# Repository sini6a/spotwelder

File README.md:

# Open Source Spot Welder

An easy-to-assemble, through-hole spot welder capable of switching high currents for welding nickel strip to lithium-ion cells. Controlled by an ATtiny13 microcontroller.

The welder is powered by a 12 V car battery or another suitable high-current battery source. The PCB, schematic, firmware, enclosure, and fabrication files are included in this repository.

> [!WARNING]
> This project switches extremely high current from a battery. Incorrect wiring, insufficient conductors, short circuits, or excessive pulse duration can cause fire, burns, damaged cells, destroyed MOSFETs, or battery failure.

## Sponsor

PCB fabrication for this project was sponsored by [PCBWay](https://www.pcbway.com/).

## Features

* **Eight-MOSFET switching bank**
  Eight IRF1404 N-channel MOSFETs are connected in parallel to switch the welding current. Each MOSFET has an individual 10 Ω gate resistor to help control switching and reduce gate ringing.

* **Dedicated MOSFET gate driver**
  An MCP1407 drives all eight MOSFET gates simultaneously. A hardware pull-down resistor on the driver input keeps the MOSFET bank off while the microcontroller is starting, resetting, or unpowered.

* **Automatic touch-to-weld triggering**
  A PC817 optocoupler-based sensing circuit detects when both welding probes are in contact with a conductive workpiece. The isolated output signals the ATtiny13 to begin the welding sequence.

* **Adjustable 1–10 ms main pulse**
  A pushbutton connected to TP4 cycles the main weld-pulse duration from 1 to 10 ms.

* **EEPROM setting storage**
  The selected weld duration is saved in the ATtiny13 EEPROM and restored after the welder is disconnected from power.

* **LED and buzzer feedback**
  The onboard LED and passive piezo buzzer provide startup, welding, and setting-change feedback. When the duration is changed, the LED flashes and the buzzer beeps once for each selected millisecond.

* **Optional double-pulse welding**
  The firmware can produce a short pre-pulse followed by the adjustable main pulse. The pre-pulse can help settle the probe contact before the main weld.

* **Separated control and power grounds**
  The high-current welding ground (`GND`) and logic ground (`CTRL_GND`) are routed separately and joined at a single net-tie point to reduce switching noise at the microcontroller.

* **Reverse-polarity protection**
  A 1N5819 Schottky diode protects the 5 V control supply if the battery input is accidentally connected with reversed polarity.

* **Transient suppression**
  Four 5.0SMDJ14A TVS diodes help clamp voltage transients generated by the welding cables and other parasitic inductance when the MOSFET bank switches off.

* **Large high-current connection pads**
  The battery and welding connections use large exposed copper pads intended for soldered or mechanically secured high-current conductors.

* **Four-layer PCB**
  Copper zones on F.Cu, In1.Cu, In2.Cu, and B.Cu help distribute the short welding-current pulses through the MOSFET bank.

> [!IMPORTANT]
> PCB copper alone should not be treated as a complete high-current busbar. Thick copper cable, copper braid, copper strip, or another suitable reinforcement is recommended for the main battery and electrode current paths.

## How it works

1. **Power input**
   A 12 V car battery or another suitable high-current battery source is connected to the `IN/OUT+` and `IN-` pads.

2. **Probe contact detection**
   When both welding probes contact the conductive workpiece, the PC817 sensing circuit produces an isolated trigger signal for the ATtiny13.

3. **Trigger validation**
   The firmware verifies that the contact signal remains active for the configured debounce period.

4. **Pre-pulse**
   When double-pulse mode is enabled, the ATtiny13 briefly activates the MCP1407 and MOSFET bank for the configured pre-pulse duration.

5. **Pulse gap**
   The MOSFETs switch off for a short interval before the main pulse.

6. **Main weld pulse**
   The MOSFET bank switches on for the selected duration between 1 and 10 ms, passing a short burst of high current through the nickel strip and cell connection.

7. **Feedback and cooldown**
   The buzzer and LED confirm that the weld sequence completed. The firmware then enforces a cooldown period and waits for the probes to be lifted before another weld can begin.

## Weld-time adjustment

TP4 is used to change the main weld-pulse duration.

Each complete button press advances the setting by 1 ms:

```text
1 → 2 → 3 → 4 → 5 → 6 → 7 → 8 → 9 → 10 → 1 ms
```

After the value changes:

* The setting is saved to EEPROM.
* The LED flashes once per selected millisecond.
* The buzzer beeps at the same time as each flash.

For example, a 6 ms setting produces six LED flashes and six beeps.

The displayed value represents the **main pulse only**. When double-pulse mode is enabled, the fixed pre-pulse is added separately.

## Firmware

The firmware is located at:

```text
Firmware/main.c
```

It directly controls:

* The MCP1407 gate-driver input
* The PC817 automatic weld trigger
* The TP4 settings button
* The status LED
* The passive piezo buzzer
* EEPROM storage for the selected duration

The firmware forces the MOSFET-driver control pin low during startup. This works together with the hardware pull-down resistor on the MCP1407 input to reduce the risk of an unintended weld pulse during reset or power-up.

### Default configuration

| Definition                | Default | Description                                          |
| ------------------------- | ------: | ---------------------------------------------------- |
| `WELD_PULSE_MIN_MS`       |    1 ms | Lowest selectable main-pulse duration                |
| `WELD_PULSE_MAX_MS`       |   10 ms | Highest selectable main-pulse duration               |
| `WELD_PULSE_DEFAULT_MS`   |    6 ms | Used when EEPROM does not contain a valid setting    |
| `USE_DOUBLE_PULSE`        |       1 | Enables the pre-pulse and main-pulse sequence        |
| `PRE_PULSE_MS`            |    3 ms | Fixed pre-pulse duration                             |
| `PULSE_GAP_MS`            |   80 ms | Delay between the pre-pulse and main pulse           |
| `WELD_COOLDOWN_MS`        |  800 ms | Minimum delay after a weld before re-arming          |
| `TRIGGER_DEBOUNCE_MS`     |   15 ms | Probe-contact validation time                        |
| `REQUIRE_TRIGGER_RELEASE` |       1 | Requires the probes to be lifted before another weld |
| `BEEP_ON_WELD_MS`         |   60 ms | Weld-confirmation tone duration                      |
| `BUZZER_ACTIVE_TYPE`      |       0 | Configures BZ1 as an externally driven passive piezo |
| `BUZZER_TONE_HZ`          | 4000 Hz | Normal feedback-tone frequency                       |

Review the values in `Firmware/main.c` before flashing, as development versions may use different pre-pulse and timing defaults.

### Building and flashing

The firmware is built with AVR-GCC and optimized for the ATtiny13's limited 1 KB program memory.

```bash
cd Firmware

make
make flash
make fuses
```

The default Makefile targets are:

| Command      | Action                                                                                                |
| ------------ | ----------------------------------------------------------------------------------------------------- |
| `make`       | Build the firmware and generate the HEX file                                                          |
| `make flash` | Flash the firmware over ISP                                                                           |
| `make fuses` | Configure the 9.6 MHz internal oscillator with the divide-by-8 fuse, resulting in a 1.2 MHz CPU clock |

The default programmer configuration may need to be changed in the Makefile when using an Arduino as ISP instead of a USBasp.

## Enclosure

A two-piece enclosure is included and was designed in FreeCAD. 3xM4 Nuts should be installed while printing the enclosure.

| Assembled                                           | Top and bottom                                                        |
| --------------------------------------------------- | --------------------------------------------------------------------- |
|  |  |

The enclosure includes:

* Four mounting bosses
* Screw-together top and bottom sections
* Side openings for the battery and electrode cables
* Source files for modification and 3D printing

Included files:

```text
Enclosure/SpotWelder.FCStd
Enclosure/Top Body.step
Enclosure/Bottom Body.step
```

## Project status

The Rev A hardware has been assembled, powered, and successfully used for spot welding.

The following core functions have been tested:

* ATtiny13 startup
* MOSFET gate-driver control
* Automatic probe-contact triggering
* Timed welding pulses
* LED feedback
* Passive buzzer feedback
* Welding from a 12 V car battery

## License

This project is licensed under the **Creative Commons Attribution-NonCommercial-ShareAlike 4.0 International license**.

See [LICENCE.md](LICENCE.md) for the complete terms.

You may build, modify, and share the design for personal and non-commercial use, provided that attribution is retained and derivative works use the same license.

Commercial production or resale of boards based on this design requires permission from Datakonsulten Sverige AB.

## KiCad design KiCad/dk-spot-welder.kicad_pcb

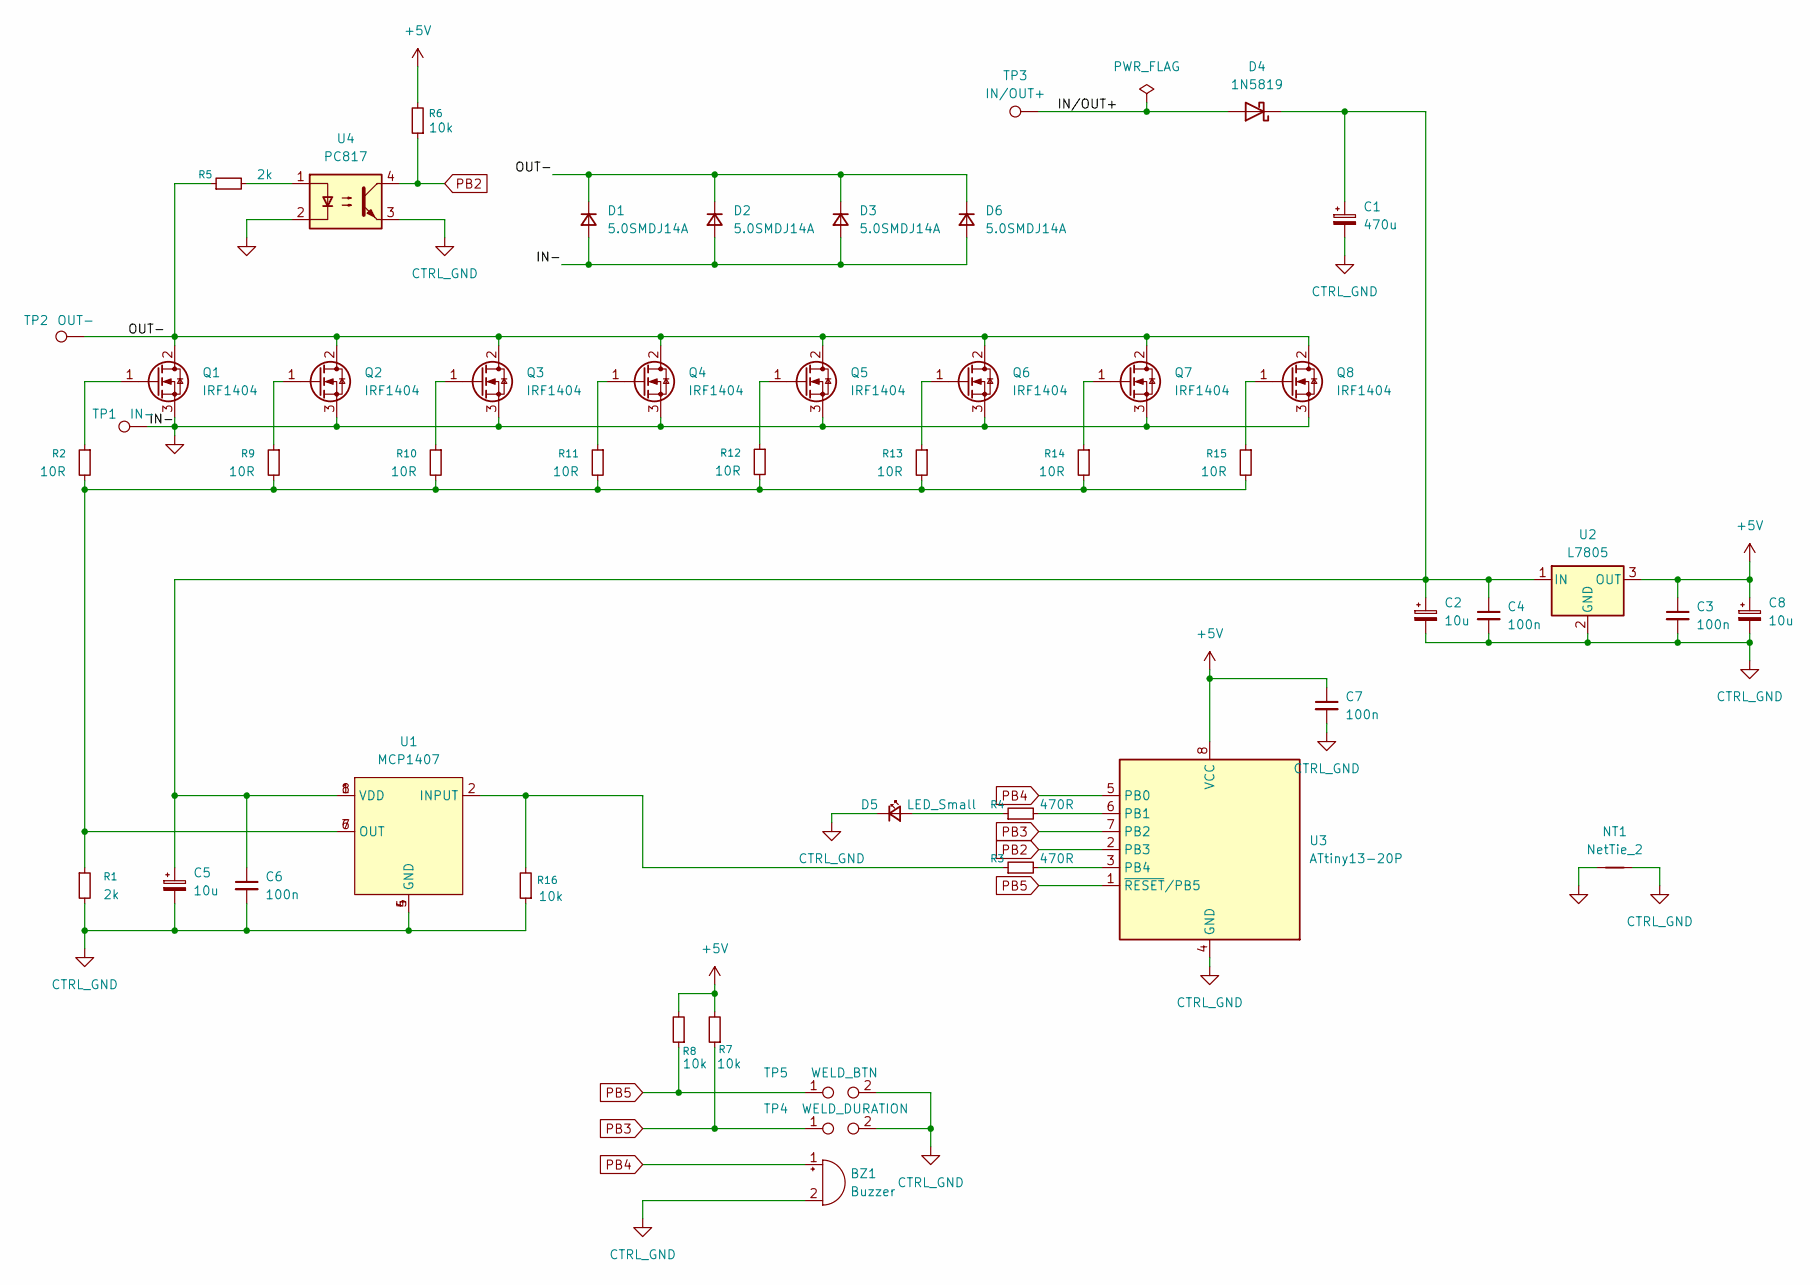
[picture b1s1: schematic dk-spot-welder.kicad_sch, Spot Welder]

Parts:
BZ1: Buzzer; Buzzer_12x9.5RM7.6
C1: 470u; CP_Radial_D10.0mm_P5.00mm
C2, C5, C8: 10u; CP_Radial_D6.3mm_P2.50mm
C3, C4, C6, C7: 100n; C_Disc_D5.0mm_W2.5mm_P5.00mm
D1, D2, D3, D6: 5.0SMDJ14A; D_SMC_Handsoldering
D4: 1N5819; D_DO-41_SOD81_P10.16mm_Horizontal
D5: LED_Small; LED_D3.0mm
NT1: NetTie_2; NetTie-2_THT_Pad1.0mm
Q1, Q2, Q3, Q4, Q5, Q6, Q7, Q8: IRF1404; TO-220-2_Horizontal_TabDown
R1, R5: 2k; R_Axial_DIN0309_L9.0mm_D3.2mm_P12.70mm_Horizontal
R2, R9, R10, R11, R12, R13, R14, R15: 10R; R_Axial_DIN0309_L9.0mm_D3.2mm_P12.70mm_Horizontal
R3, R4: 470R; R_Axial_DIN0309_L9.0mm_D3.2mm_P12.70mm_Horizontal
R6, R7, R8, R16: 10k; R_Axial_DIN0309_L9.0mm_D3.2mm_P12.70mm_Horizontal
TP1: IN-; MountingHole_4mm_Pad_Via
TP2: OUT-; MountingHole_4mm_Pad_Via
TP3: IN/OUT+; MountingHole_4mm_Pad_Via
TP4: WELD_DURATION; TestPoint_2Pads_Pitch5.08mm_Drill1.3mm
TP5: WELD_BTN; TestPoint_2Pads_Pitch5.08mm_Drill1.3mm
U1: MCP1407; DIP-8_W7.62mm
U2: L7805; TO-220-3_Horizontal_TabDown
U3: ATtiny13-20P; DIP-8_W7.62mm
U4: PC817; DIP-4_W7.62mm

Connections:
+5V: C3.1, C7.1, C8.1, R6.2, R7.2, R8.2, U2.3 (OUT), U3.8 (VCC)
/IN/OUT+: D4.2 (A), TP3.1 (1_1)
/OUT-: D1.1 (K), D2.1 (K), D3.1 (K), D6.1 (K), Q1.2 (D), Q2.2 (D), Q3.2 (D), Q4.2 (D), Q5.2 (D), Q6.2 (D), Q7.2 (D), Q8.2 (D), R5.1, TP2.1 (1_1)
CTRL_GND: BZ1.2 (-), C1.2, C2.2, C3.2, C4.2, C5.2, C6.2, C7.2, C8.2, D5.1 (K), NT1.2, R1.2, R16.1, TP4.2, TP5.2, U1.4 (GND), U1.5 (GND), U2.2 (GND), U3.4 (GND), U4.3
GND: D1.2 (A), D2.2 (A), D3.2 (A), D6.2 (A), NT1.1, Q1.3 (S), Q2.3 (S), Q3.3 (S), Q4.3 (S), Q5.3 (S), Q6.3 (S), Q7.3 (S), Q8.3 (S), TP1.1 (1_1), U4.2
unnamed: C1.1, C2.1, C4.1, C5.1, C6.1, D4.1 (K), U1.1 (VDD), U1.8 (VDD), U2.1 (IN)
unnamed: D5.2 (A), R4.1
unnamed: Q1.1 (G), R2.1
unnamed: Q2.1 (G), R9.1
unnamed: Q3.1 (G), R10.1
unnamed: Q4.1 (G), R11.1
unnamed: Q5.1 (G), R12.1
unnamed: Q6.1 (G), R13.1
unnamed: Q7.1 (G), R14.1
unnamed: Q8.1 (G), R15.1
unnamed: R1.1, R2.2, R9.2, R10.2, R11.2, R12.2, R13.2, R14.2, R15.2, U1.6 (OUT), U1.7 (OUT)
unnamed: R5.2, U4.1
unnamed: R3.1, R16.2, U1.2 (INPUT)
unnamed: R4.2, U3.6 (PB1)
unnamed: R3.2, U3.3 (PB4)
PB2: R6.1, U3.2 (PB3), U4.4
PB3: R7.1, TP4.1, U3.7 (PB2)
PB4: BZ1.1 (+), U3.5 (PB0)
PB5: R8.1, TP5.1, U3.1 (~RESET/PB5)

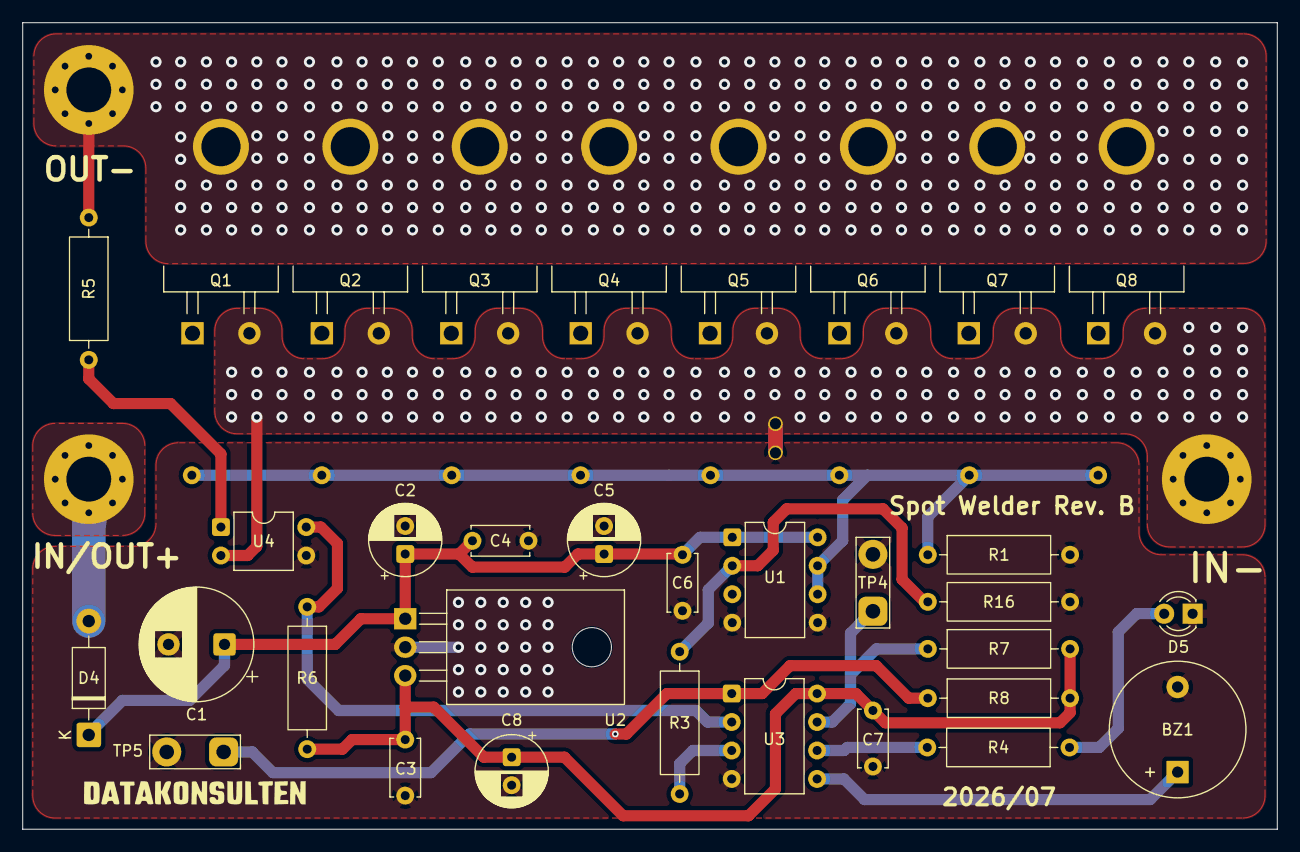
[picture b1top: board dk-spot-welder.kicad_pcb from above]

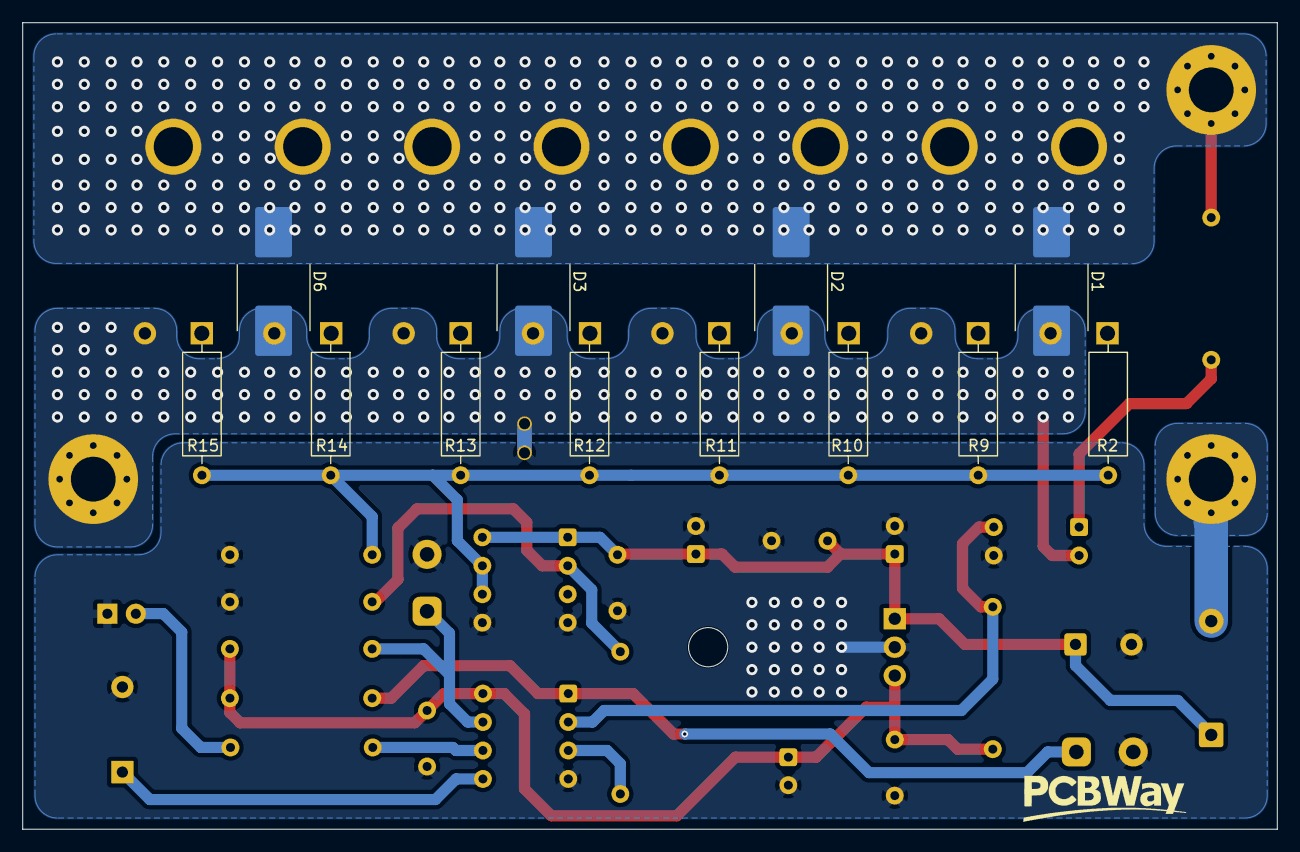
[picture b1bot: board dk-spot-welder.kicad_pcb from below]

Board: 4 copper layers, 112.0 x 72.0 mm, 49 parts (12 on the bottom side), 24 nets.

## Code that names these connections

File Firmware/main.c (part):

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 * Datakonsulten Spot Welder - ATtiny13-20P firmware
 *
 * Pin mapping (derived from KiCad/dk-spot-welder.kicad_sch, U3):
 *   PB0 (pin 5) -> BZ1   buzzer, active HIGH, no series resistor (active/self-oscillating
 *                  piezo buzzer assumed - see BUZZER_ACTIVE_TYPE below)
 *   PB1 (pin 6) -> D5    status LED via R4, active HIGH
 *   PB2 (pin 7) -> TP4   manual trigger button header, external pull-up R7 to +5V,
 *                  active LOW (button pulls to CTRL_GND when pressed)
 *   PB3 (pin 2) -> U4    PC817 phototransistor output, external pull-up R6 to +5V,
 *                  active LOW (opto conducts when welding tips touch the workpiece)
 *   PB4 (pin 3) -> R3 -> U1 MCP1407 INPUT, active HIGH = MOSFET bank ON (welding current
 *                  flowing). R16 hardware-pulls this net low at the driver input as a
 *                  fail-safe, but firmware also forces PB4 low before anything else runs.
 *   PB5 (pin 1) -> RESET, pulled up by R8. Not used as GPIO.
 *
 * All user-tunable parameters are grouped at the top of this file.
 */
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/* ================================================================= */

/* --- Pin assignments (see header comment for derivation) --- */
#define PIN_BUZZER  PB0
#define PIN_LED     PB1
#define PIN_BTN     PB2   /* TP4 weld-duration settings button, active LOW */
#define PIN_OPTO    PB3   /* automatic tip-touch trigger, via U4/PC817 */
#define PIN_WELD    PB4   /* MOSFET bank enable, via U1/MCP1407 */

/* Millisecond delay built from a compile-time-constant _delay_us() call per iteration,
   rather than a single runtime _delay_ms() call, to keep code size small on the
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}

/*
 * Play a tone using Timer0 and the OC0A hardware output on PB0.
 *
 * PB0 is OC0A on the ATtiny13. Timer0 toggles the pin automatically,
 * so the CPU only has to wait for the requested duration.
 */
static void passive_tone(uint8_t timer_value, uint16_t duration_ms)
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     * CTC mode:
     * WGM01 = 1
     *
     * Toggle OC0A/PB0 each time the timer reaches OCR0A:
     * COM0A0 = 1
     */
    TCCR0A = (1 << COM0A0) | (1 << WGM01);
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    /* Stop Timer0. */
    TCCR0B = 0;

    /* Disconnect Timer0 from PB0. */
    TCCR0A = 0;

    /* Guarantee that the buzzer finishes LOW. */
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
